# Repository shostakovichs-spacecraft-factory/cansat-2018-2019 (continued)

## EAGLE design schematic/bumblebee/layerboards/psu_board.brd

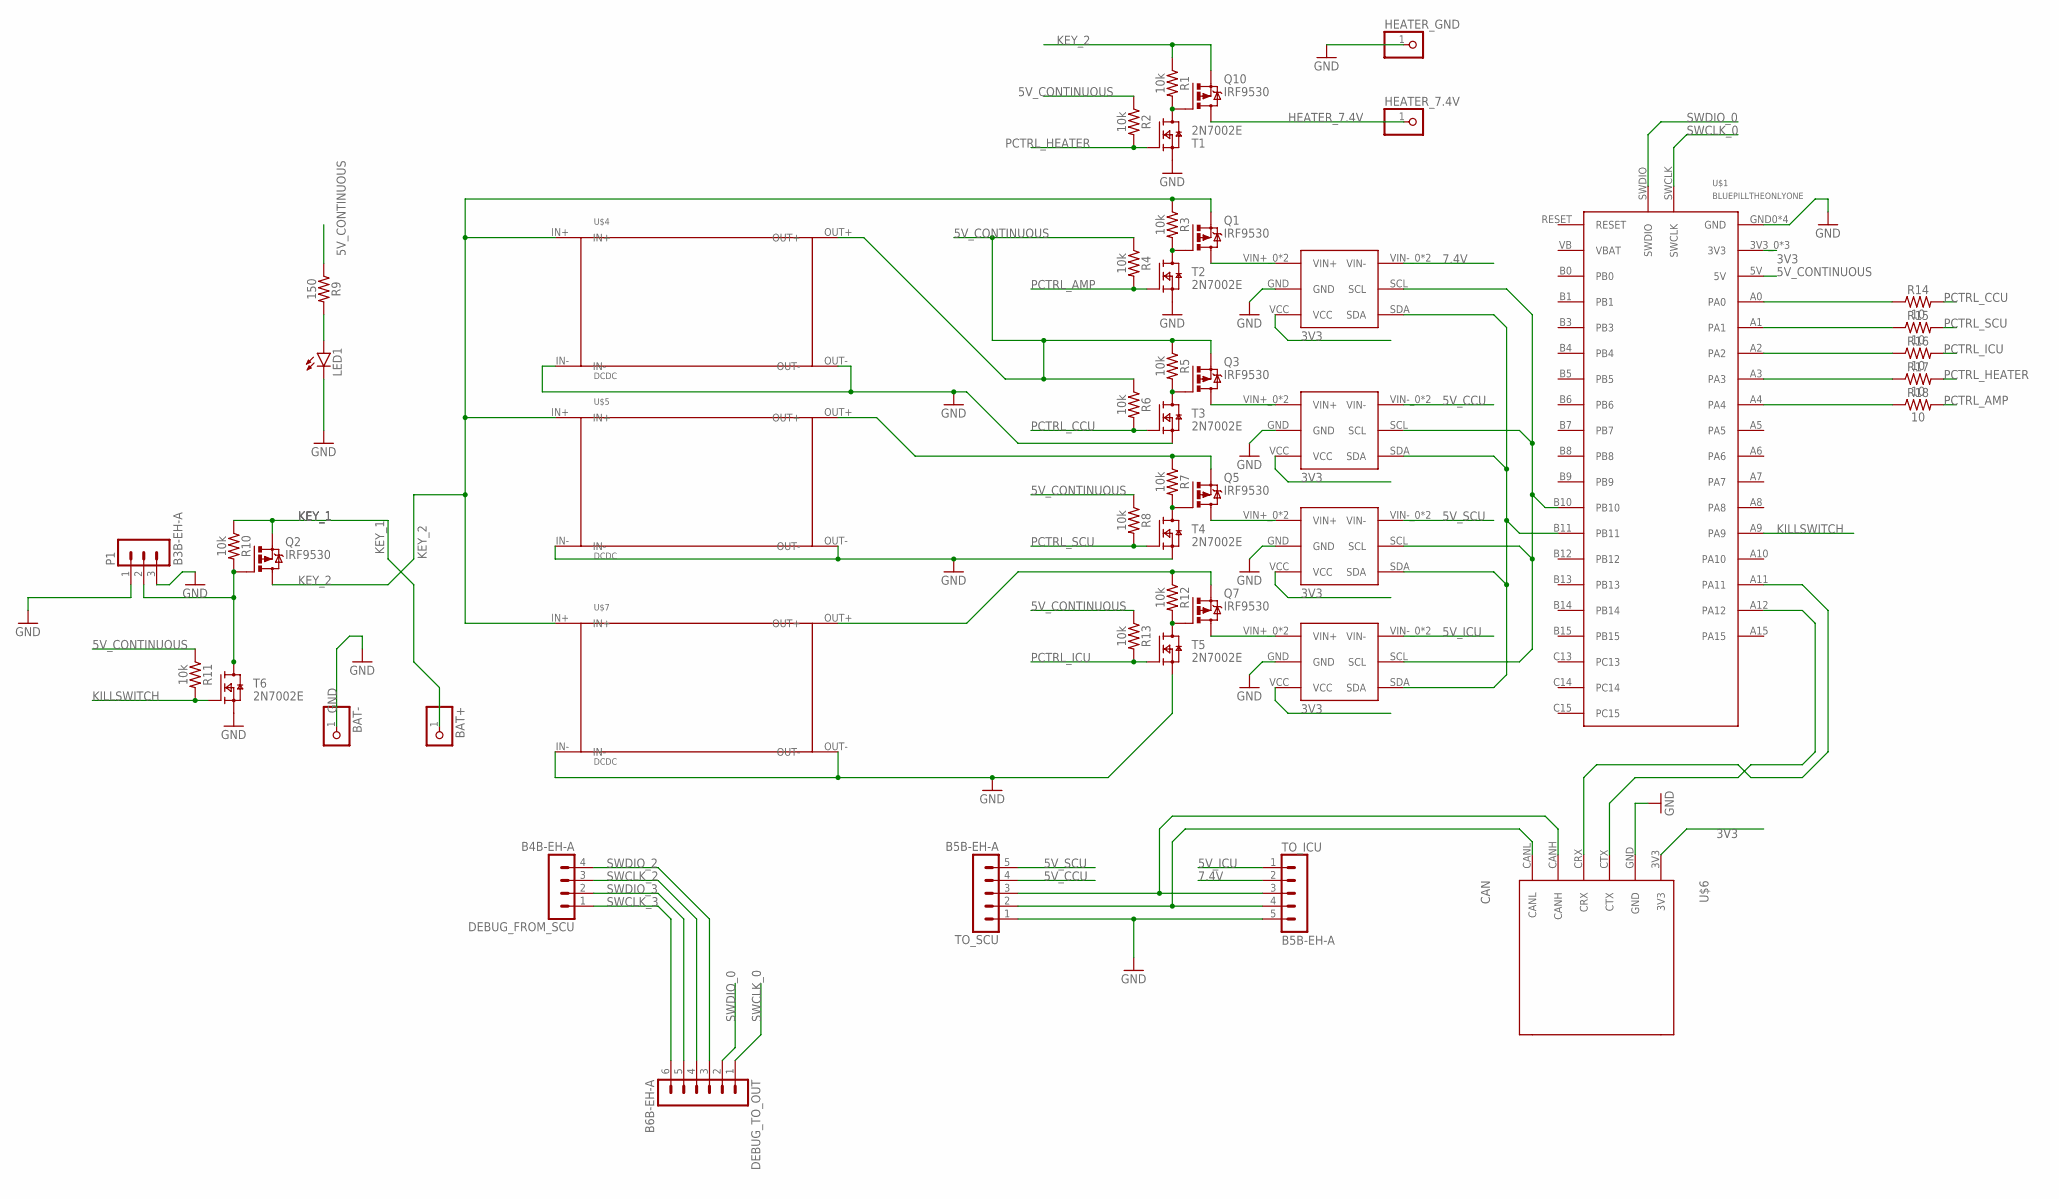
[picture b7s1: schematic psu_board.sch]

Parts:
BAT+: PINHD-1X1; 1X01
BAT-: PINHD-1X1; 1X01
DEBUG_FROM_SCU: B4B-EH-A
DEBUG_TO_OUT: B6B-EH-A
HEATER_7.4V: PINHD-1X1; 1X01
HEATER_GND: PINHD-1X1; 1X01
LED1: LED5MM
P1: B3B-EH-A
Q1, Q2, Q3, Q5, Q7, Q10: IRF9530; TO220BV
R1, R2, R3, R4, R5, R6, R7, R8, R10, R11, R12, R13: 10k; AXIAL-0.3
R9: 150; AXIAL-0.3
R14, R15, R16, R17, R18: 10; AXIAL-0.3
T1, T2, T3, T4, T5, T6: 2N7002E; SOT23
TO_ICU: B5B-EH-A
TO_SCU: B5B-EH-A
U$1: BLUEPILLTHEONLYONE; BLUEPIL
U$2, U$3, U$8, U$9: INA
U$4, U$5, U$7: DCDC
U$6: CAN

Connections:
3V3: U$1.3V3_0 (3V3), U$1.3V3_1 (3V3), U$1.3V3_2 (3V3), U$2.VCC, U$3.VCC, U$6.3V3, U$8.VCC, U$9.VCC
5V_CCU: TO_SCU.4, U$9.VIN-_0 (VIN-), U$9.VIN-_1 (VIN-)
5V_CONTINUOUS: Q3.S, R2.P$1 (1), R4.P$1 (1), R5.P$1 (1), R6.P$1 (1), R8.P$1 (1), R9.P$1 (1), R11.P$1 (1), R13.P$1 (1), U$1.5V, U$4.OUT+
5V_ICU: TO_ICU.1, U$2.VIN-_0 (VIN-), U$2.VIN-_1 (VIN-)
5V_SCU: TO_SCU.5, U$8.VIN-_0 (VIN-), U$8.VIN-_1 (VIN-)
7.4V: TO_ICU.2, U$3.VIN-_0 (VIN-), U$3.VIN-_1 (VIN-)
CANH: TO_ICU.3, TO_SCU.3, U$6.CANH
CANL: TO_ICU.4, TO_SCU.2, U$6.CANL
GND: BAT-.1, HEATER_GND.1, LED1.K (C), P1.1, P1.3, T1.2 (S), T2.2 (S), T3.2 (S), T4.2 (S), T5.2 (S), T6.2 (S), TO_ICU.5, TO_SCU.1, U$1.GND0 (GND), U$1.GND1 (GND), U$1.GND2 (GND), U$1.GND3 (GND), U$2.GND, U$3.GND, U$4.IN-, U$4.OUT-, U$5.IN-, U$5.OUT-, U$6.GND, U$7.IN-, U$7.OUT-, U$8.GND, U$9.GND
HEATER_7.4V: HEATER_7.4V.1, Q10.D
KEY_1: BAT+.1, Q2.S, R10.P$1 (1)
KEY_2: Q1.S, Q2.D, Q10.S, R1.P$1 (1), R3.P$1 (1), U$4.IN+, U$5.IN+, U$7.IN+
KILLSWITCH: R11.P$2 (2), T6.1 (G), U$1.A9
unnamed: Q1.G, R3.P$2 (2), T2.3 (D)
unnamed: U$1.A11, U$6.CRX
unnamed: Q5.G, R7.P$2 (2), T4.3 (D)
unnamed: Q7.G, R12.P$2 (2), T5.3 (D)
unnamed: Q5.S, R7.P$1 (1), U$5.OUT+
unnamed: Q3.G, R5.P$2 (2), T3.3 (D)
unnamed: Q7.S, R12.P$1 (1), U$7.OUT+
unnamed: Q1.D, U$3.VIN+_0 (VIN+), U$3.VIN+_1 (VIN+)
unnamed: Q3.D, U$9.VIN+_0 (VIN+), U$9.VIN+_1 (VIN+)
unnamed: Q5.D, U$8.VIN+_0 (VIN+), U$8.VIN+_1 (VIN+)
unnamed: Q7.D, U$2.VIN+_0 (VIN+), U$2.VIN+_1 (VIN+)
unnamed: U$1.B11, U$2.SDA, U$3.SDA, U$8.SDA, U$9.SDA
unnamed: U$1.B10, U$2.SCL, U$3.SCL, U$8.SCL, U$9.SCL
unnamed: U$1.A12, U$6.CTX
unnamed: LED1.A, R9.P$2 (2)
unnamed: Q10.G, R1.P$2 (2), T1.3 (D)
unnamed: R14.P$1 (1), U$1.A0
unnamed: R15.P$1 (1), U$1.A1
unnamed: R16.P$1 (1), U$1.A2
unnamed: R17.P$1 (1), U$1.A3
unnamed: R18.P$1 (1), U$1.A4
unnamed: P1.2, Q2.G, R10.P$2 (2), T6.3 (D)
PCTRL_AMP: R4.P$2 (2), R18.P$2 (2), T2.1 (G)
PCTRL_CCU: R6.P$2 (2), R14.P$2 (2), T3.1 (G)
PCTRL_HEATER: R2.P$2 (2), R17.P$2 (2), T1.1 (G)
PCTRL_ICU: R13.P$2 (2), R16.P$2 (2), T5.1 (G)
PCTRL_SCU: R8.P$2 (2), R15.P$2 (2), T4.1 (G)
SWCLK_0: DEBUG_TO_OUT.1, U$1.SWCLK
SWCLK_2: DEBUG_FROM_SCU.3, DEBUG_TO_OUT.4
SWCLK_3: DEBUG_FROM_SCU.1, DEBUG_TO_OUT.6
SWDIO_0: DEBUG_TO_OUT.2, U$1.SWDIO
SWDIO_2: DEBUG_FROM_SCU.4, DEBUG_TO_OUT.3
SWDIO_3: DEBUG_FROM_SCU.2, DEBUG_TO_OUT.5

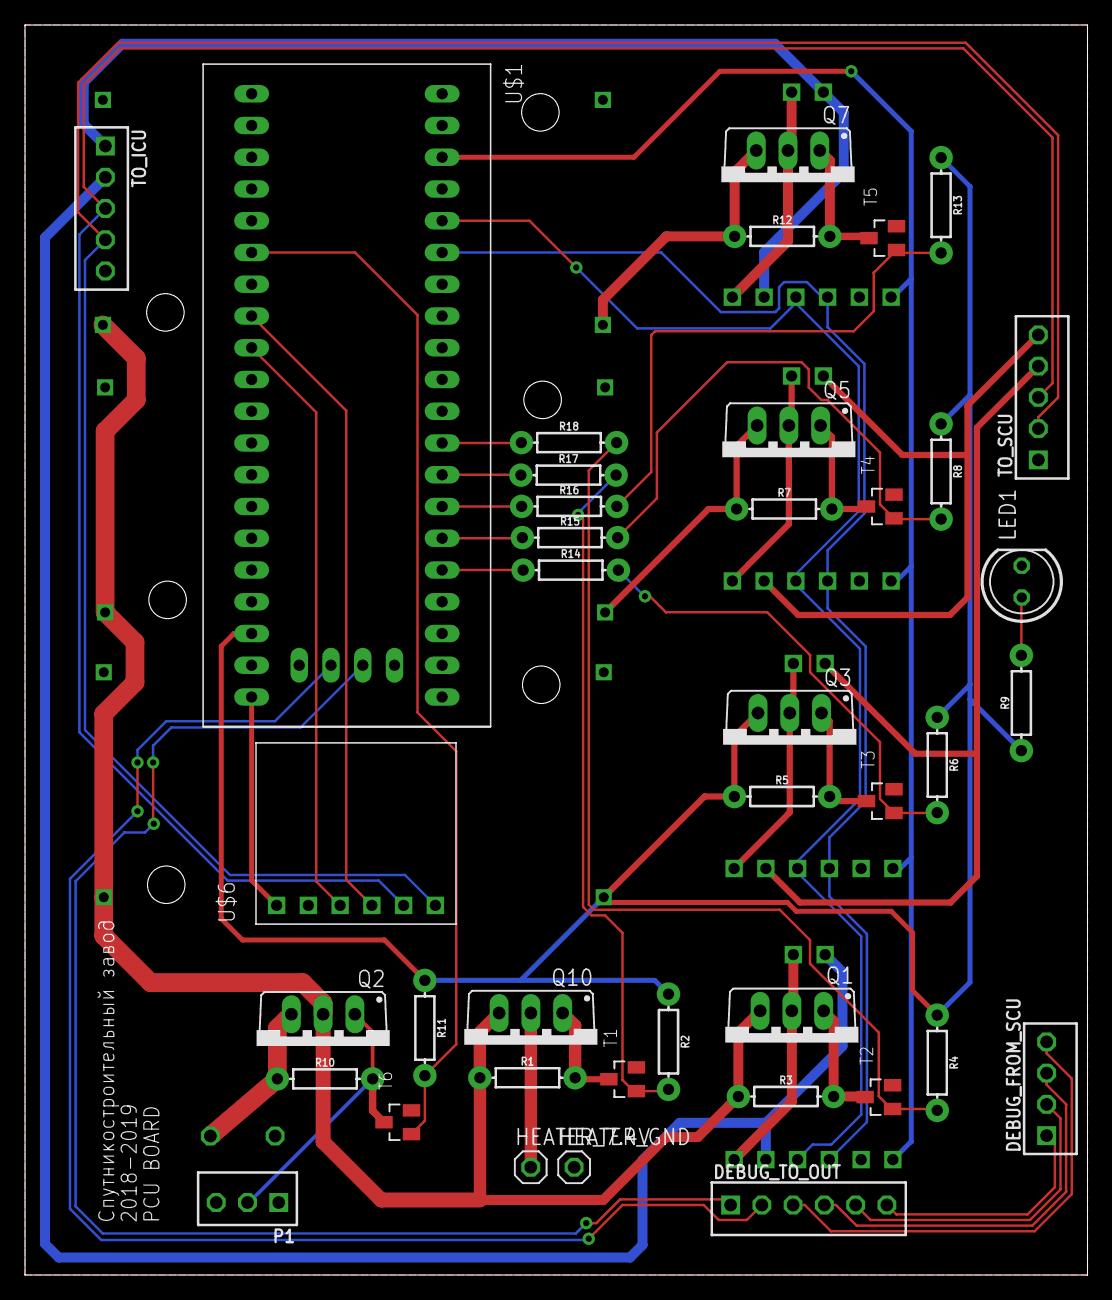
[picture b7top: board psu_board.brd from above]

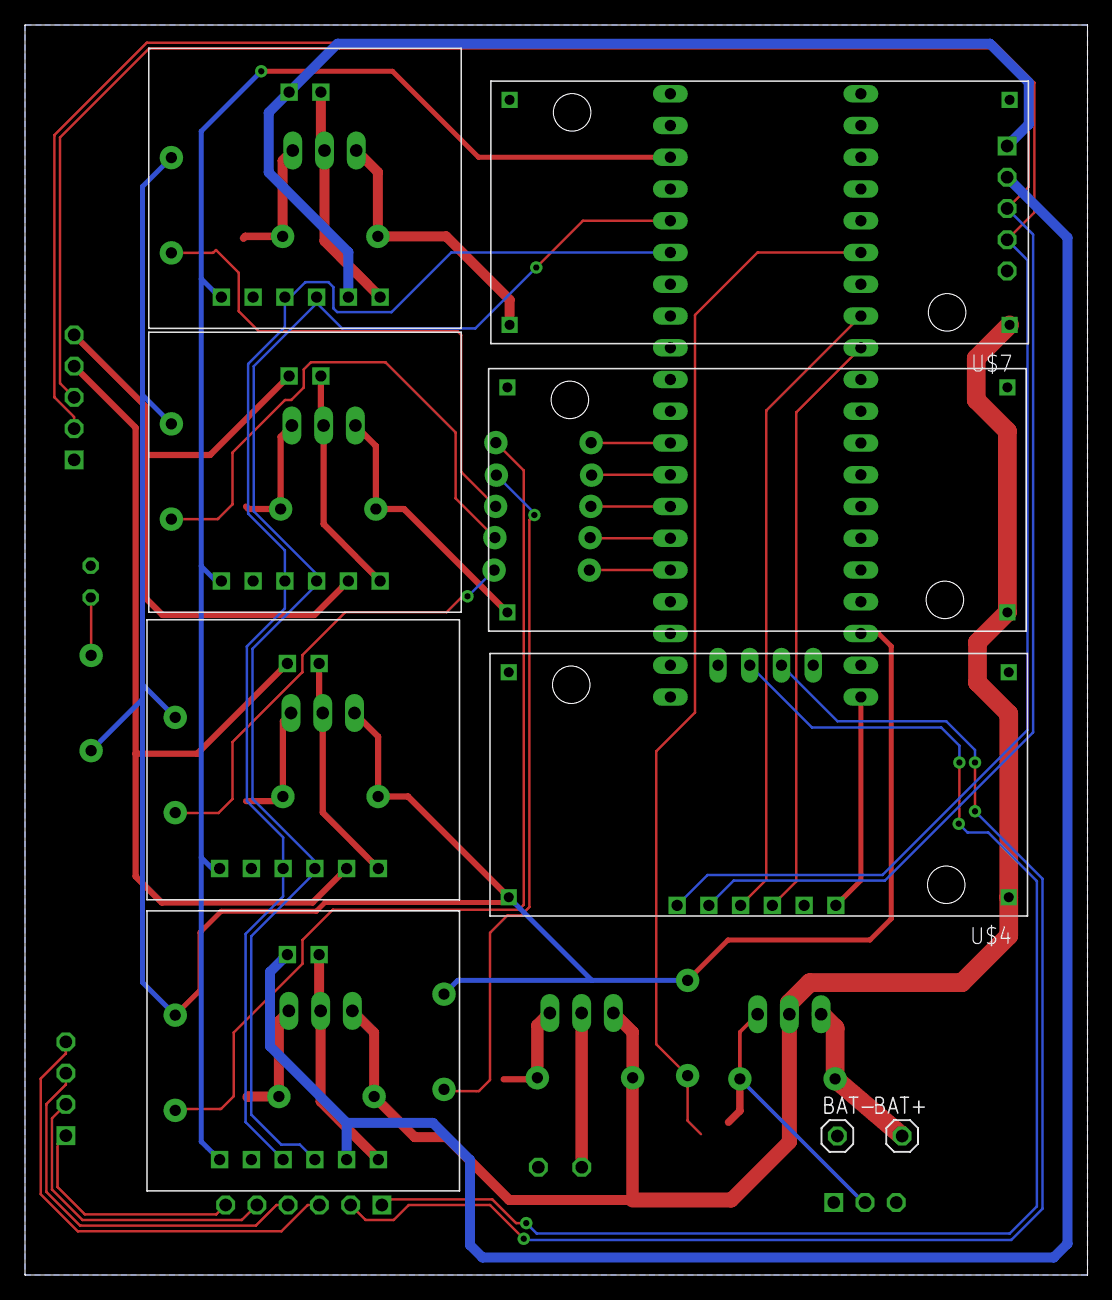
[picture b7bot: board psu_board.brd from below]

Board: 2 copper layers, 85.0 x 100.0 mm, 49 parts (9 on the bottom side), 46 nets.

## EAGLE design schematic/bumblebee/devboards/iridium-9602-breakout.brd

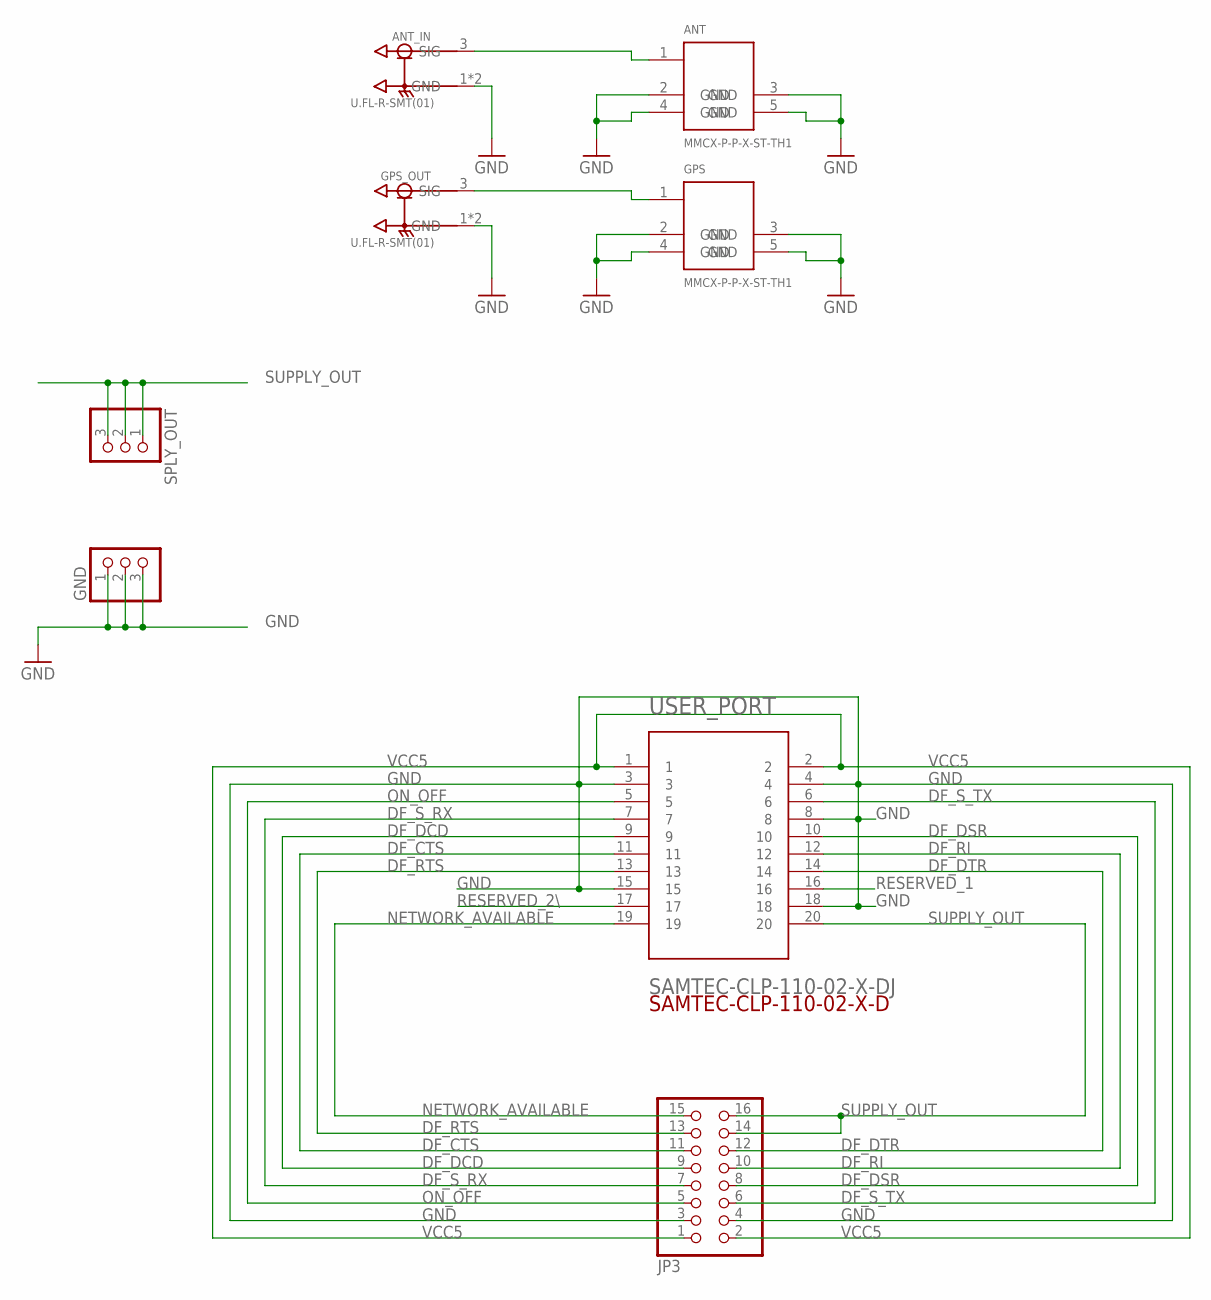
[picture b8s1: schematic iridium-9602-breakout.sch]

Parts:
ANT: MMCX-P-P-X-ST-TH1
ANT_IN: U.FL-R-SMT(01); HRS_U.FL-R-SMT(01)
GND: PINHD-1X3; 1X03
GPS: MMCX-P-P-X-ST-TH1
GPS_OUT: U.FL-R-SMT(01); HRS_U.FL-R-SMT(01)
JP3: PINHD-2X8; 2X08
SPLY_OUT: PINHD-1X3; 1X03
USER_PORT: SAMTEC-CLP-110-02-X-DJ; SAMTEC-CLP-110-02-X-D

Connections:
DF_CTS: JP3.11, USER_PORT.11
DF_DCD: JP3.9, USER_PORT.9
DF_DSR: JP3.8, USER_PORT.10
DF_DTR: JP3.12, USER_PORT.14
DF_RI: JP3.10, USER_PORT.12
DF_RTS: JP3.13, USER_PORT.13
DF_S_RX: JP3.7, USER_PORT.7
DF_S_TX: JP3.6, USER_PORT.6
GND: ANT.2 (GND), ANT.3 (GND), ANT.4 (GND), ANT.5 (GND), ANT_IN.1 (GND), ANT_IN.2 (GND), GND.1, GND.2, GND.3, GPS.2 (GND), GPS.3 (GND), GPS.4 (GND), GPS.5 (GND), GPS_OUT.1 (GND), GPS_OUT.2 (GND), JP3.3, JP3.4, USER_PORT.3, USER_PORT.4, USER_PORT.8, USER_PORT.15, USER_PORT.18
unnamed: ANT.1, ANT_IN.3 (SIG)
unnamed: GPS.1, GPS_OUT.3 (SIG)
NETWORK_AVAILABLE: JP3.15, USER_PORT.19
ON_OFF: JP3.5, USER_PORT.5
RESERVED_1: USER_PORT.16
RESERVED_2\: USER_PORT.17
SUPPLY_OUT: JP3.14, JP3.16, SPLY_OUT.1, SPLY_OUT.2, SPLY_OUT.3, USER_PORT.20
VCC5: JP3.1, JP3.2, USER_PORT.1, USER_PORT.2

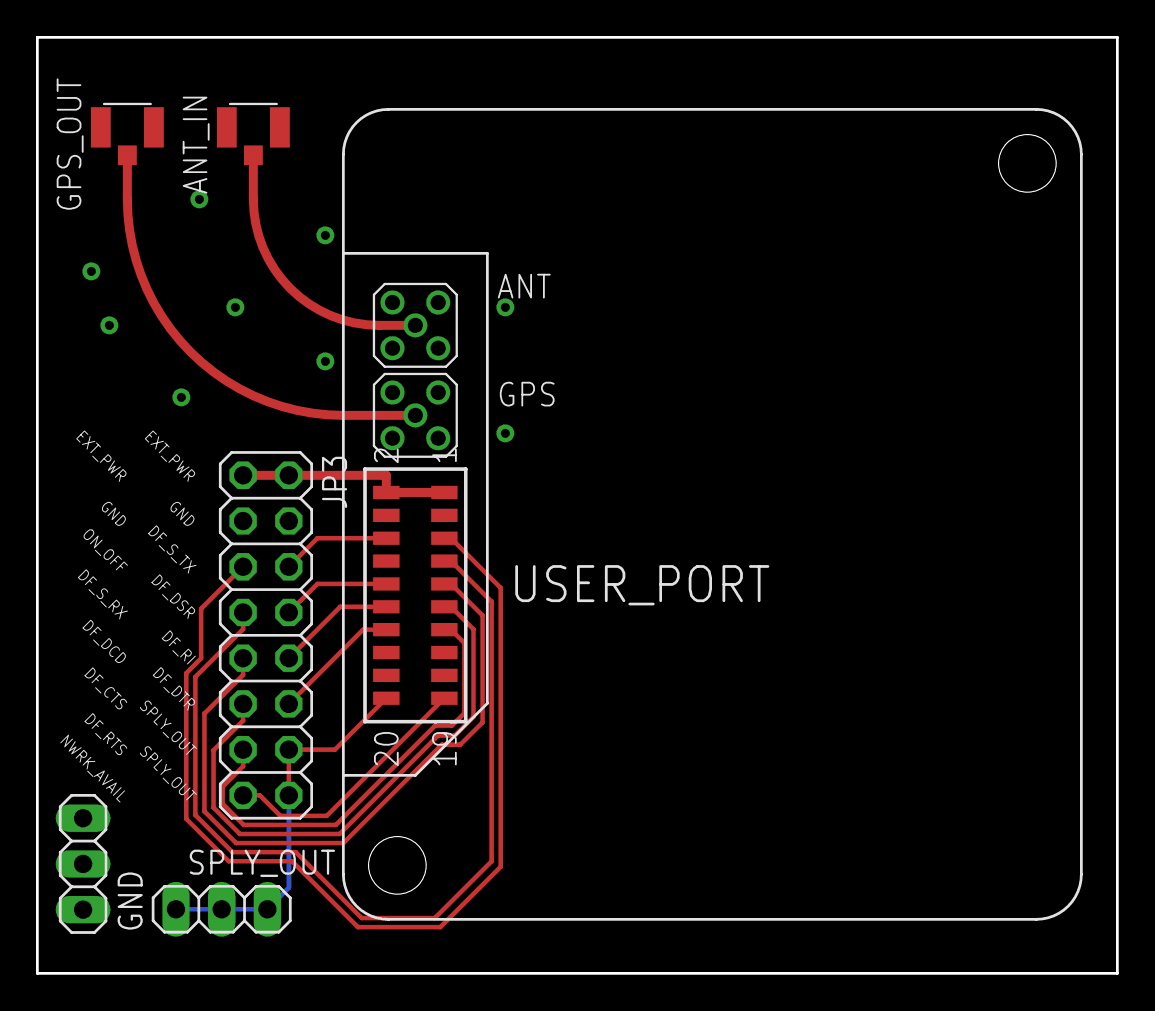
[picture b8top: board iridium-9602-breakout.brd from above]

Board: 2 copper layers, 60.0 x 52.0 mm, 8 parts (0 on the bottom side), 15 nets.

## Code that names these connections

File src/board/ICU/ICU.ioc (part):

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Mcu.Name=STM32F103V(C-D-E)Tx
Mcu.Package=LQFP100
Mcu.UserName=STM32F103VCTx
PA13.Mode=Serial_Wire
PA13.Signal=SYS_JTMS-SWDIO
PA14.Mode=Serial_Wire
PA14.Signal=SYS_JTCK-SWCLK
PB12.GPIOParameters=PinState,GPIO_Label
PB12.GPIO_Label=RADIO_NSS
PB12.PinState=GPIO_PIN_SET
PB12.Signal=GPIO_Output
PB13.Mode=Full_Duplex_Master
PB13.Signal=SPI2_SCK
PB14.Mode=Full_Duplex_Master
PB14.Signal=SPI2_MISO
PB15.Mode=Full_Duplex_Master
PB15.Signal=SPI2_MOSI
PB6.GPIOParameters=GPIO_Speed,PinState,GPIO_Label
PB6.GPIO_Label=LEDPIN
PB6.GPIO_Speed=GPIO_SPEED_FREQ_LOW
PB6.PinState=GPIO_PIN_RESET
PB6.Signal=GPIO_Output
PC10.Mode=SD_4_bits_Wide_bus
PC10.Signal=SDIO_D2
PC11.Mode=SD_4_bits_Wide_bus
PC11.Signal=SDIO_D3
PC12.Mode=SD_4_bits_Wide_bus
PC12.Signal=SDIO_CK
PC8.Mode=SD_4_bits_Wide_bus
PC8.Signal=SDIO_D0
PC9.Mode=SD_4_bits_Wide_bus
PC9.Signal=SDIO_D1
PD0.Mode=Master
PD0.Signal=CAN_RX
PD1.Mode=Master
PD1.Signal=CAN_TX
PD15.GPIOParameters=GPIO_Label
PD15.GPIO_Label=RADIO_IRQ
PD15.Signal=GPXTI15
PD2.Mode=SD_4_bits_Wide_bus
PD2.Signal=SDIO_CMD
PE12.GPIOParameters=GPIO_Label
PE12.GPIO_Label=RADIO_BUSY
PE12.Signal=GPIO_Input
PE13.GPIOParameters=GPIO_Speed,GPIO_Label
PE13.GPIO_Label=RADIO_TXEN
PE13.GPIO_Speed=GPIO_SPEED_FREQ_LOW
PE13.Signal=GPIO_Output
PE14.GPIOParameters=PinState,GPIO_Label,GPIO_ModeDefaultOutputPP
PE14.GPIO_Label=RADIO_NRST
PE14.GPIO_ModeDefaultOutputPP=GPIO_MODE_OUTPUT_OD
PE14.PinState=GPIO_PIN_SET
PE14.Signal=GPIO_Output
PE15.GPIOParameters=GPIO_Label
PE15.GPIO_Label=RADIO_RXEN
PE15.Signal=GPIO_Output
RCC.SYSCLKFreq_VALUE=72000000
RCC.SYSCLKSource=RCC_SYSCLKSOURCE_PLLCLK
board=custom

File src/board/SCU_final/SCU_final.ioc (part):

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Mcu.Name=STM32F103C(8-B)Tx
Mcu.Package=LQFP48
Mcu.UserName=STM32F103C8Tx
PA11.Mode=Master
PA11.Signal=CAN_RX
PA12.Mode=Master
PA12.Signal=CAN_TX
PA13.Mode=Serial_Wire
PA13.Signal=SYS_JTMS-SWDIO
PA14.Mode=Serial_Wire
PA14.Signal=SYS_JTCK-SWCLK
PA4.GPIOParameters=GPIO_Speed,PinState,GPIO_Label
PA4.GPIO_Label=BME_CS
PA4.GPIO_Speed=GPIO_SPEED_FREQ_HIGH
PA4.PinState=GPIO_PIN_SET
PA4.Signal=GPIO_Output
PA5.GPIOParameters=GPIO_Label
PA5.GPIO_Label=BME_SCK
PA5.Mode=Full_Duplex_Master
PA5.Signal=SPI1_SCK
PA6.GPIOParameters=GPIO_Label
PA6.GPIO_Label=BME_MISO
PA6.Mode=Full_Duplex_Master
PA6.Signal=SPI1_MISO
PA7.GPIOParameters=GPIO_Label
PA7.GPIO_Label=BME_MOSI
PA7.Mode=Full_Duplex_Master
PA7.Signal=SPI1_MOSI
PB10.GPIOParameters=GPIO_Label
PB10.GPIO_Label=MAG_SCL
PB10.Mode=I2C
PB10.Signal=I2C2_SCL
PB11.GPIOParameters=GPIO_Label
PB11.GPIO_Label=MAG_SDA
PB11.Mode=I2C
PB11.Signal=I2C2_SDA
PB12.GPIOParameters=GPIO_Speed,PinState,GPIO_Label
PB12.GPIO_Label=LSM_CS
PB12.GPIO_Speed=GPIO_SPEED_FREQ_HIGH
PB12.PinState=GPIO_PIN_SET
PB12.Signal=GPIO_Output
PB13.GPIOParameters=GPIO_Label
PB13.GPIO_Label=LSM_SCK
PB13.Mode=Full_Duplex_Master
PB13.Signal=SPI2_SCK
PB14.GPIOParameters=GPIO_Label
PB14.GPIO_Label=LSM_MISO
PB14.Mode=Full_Duplex_Master
PB14.Signal=SPI2_MISO
PB15.GPIOParameters=GPIO_Label
PB15.GPIO_Label=LSM_MOSI
PB15.Mode=Full_Duplex_Master
PB15.Signal=SPI2_MOSI
PB6.GPIOParameters=GPIO_Label
PB6.GPIO_Label=ADC_SCL
PB6.Mode=I2C
PB6.Signal=I2C1_SCL
PB7.GPIOParameters=GPIO_Label
PB7.GPIO_Label=ADC_SDA
PB7.Mode=I2C
PB7.Signal=I2C1_SDA
PC13-TAMPER-RTC.GPIOParameters=GPIO_Speed,PinState,GPIO_Label,GPIO_ModeDefaultOutputPP
PC13-TAMPER-RTC.GPIO_Label=LED
PC13-TAMPER-RTC.GPIO_ModeDefaultOutputPP=GPIO_MODE_OUTPUT_OD
PC13-TAMPER-RTC.GPIO_Speed=GPIO_SPEED_FREQ_HIGH
PC13-TAMPER-RTC.PinState=GPIO_PIN_SET
PC13-TAMPER-RTC.Signal=GPIO_Output
PD0-OSC_IN.Mode=HSE-External-Oscillator
PD0-OSC_IN.Signal=RCC_OSC_IN
PD1-OSC_OUT.Mode=HSE-External-Oscillator
PD1-OSC_OUT.Signal=RCC_OSC_OUT
RCC.SYSCLKFreq_VALUE=72000000
RCC.SYSCLKSource=RCC_SYSCLKSOURCE_PLLCLK
board=custom

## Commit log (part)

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2018-10-16 Папочка для моделей
2018-10-19 Add files via upload
    Часть деталек для тестов и замоделенная начинка
2018-10-21 Пара изменений
2018-11-15 Moving files
2018-11-16 Код поиска Солнца для модели
2018-11-17 Remake all light system && add graphic component
    Add new class for all light system functions
    It was important to make system much easier. So now you have to create
    new class instance, call just one function and be careful when it
    returns not a number
    Add graphic component
    Now you able to get all useful information from starting
2018-11-17 В тесте маджвика магнитометр на I2C
2018-11-17 Фоторезистор вынесен в отдельный модуль
2018-11-17 Изменение порядка сенсоров
2018-11-23 добавили тестовый проект для сериал порта на линуксе
2018-11-28 Создание интерфеса неспектральных камер
    Создан интерфейс для работы с uart под linux.
    Пока что нет способа изменить конфигурацию без перекомпиляции программы.
    Создан интерфейс для работы с камерами.
    Это прототип, так как не способен работать. Некоторые функции не
    подходят для работы на борту. Пока нет способа менять концигурацию во
    время выполения программы. Известные баги:
2018-11-29 Исправление ошибок
    - Наименование функции чтения изображения camera_get_and_save_picture
    изменена на camera_load_and_save_picture.
    - Теперь все функции делают то, что от них хотят.
    - Увеличен размер строки имени файла для уарта на 1.
2018-12-08 Добавление пары функции для удобной работы на миникомпьютере Рнаьше была лишь одна функция для сохранения изображения. Она загружала и сразу сохраняла его, занимая все процессорное время. Теперь есть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
2018-12-11 Добавлвены требования к надежности (их нет) Добавлены требования к живучести НИП-а Поправлена структура ТЗ
2018-12-22 Наработки Арины для схемы
2018-12-28 Реструткуризация иглового проекта
2018-12-28 Добавление описания взаимодействия протоколов
    В целом, описано, где какой протокол используется. Есть пара элементов, которые стоило бы доделать. Также не уверен в необходимости описания самих протоколов. Поэтому их тут нет.
2018-12-28 Обновление схемы протоколов
    Сделал схему красивее
2018-12-29 Полная переработка описания протоколов
    Все переделано с учетом всех замечаний
2019-01-03 Мелкие изменения
    Новая цветовая гамма. Добавлена главная страница. Маленькие корректировки.
2019-01-06 Squashed commit of the following:
    commit bbe75f2ba636e86ea759fc0c795d406c2297ca99
    Author: Kirs67 <kirilel200267@gmail.com>
    Date: Mon Jan 7 01:16:28 2019 +0300
    Исправлена INA
    commit 84fcf59dae87e7c5b0b953ea137079167e3747d4
    Author: Kirs67 <kirilel200267@gmail.com>
2019-01-09 Модель аппарата на момент 09.01.19
    apparat.asm -- сборка аппарата, остальное -- его элементы
2019-01-10 Добавил протокол совещания (!) от 10.01.18
2019-01-11 Добавлена схема платы SCU
2019-01-11 Комментарии в презентации по обсуждениям
2019-01-14 Платка для отладки радиомодуля
2019-01-14 Визуальное улучшение
    Я познал красоту. Теперь вы можете увидеть, насколько стало яснее, приятнее и точнее.
2019-01-15 Платка для антенны иридиума
2019-01-16 Мелкие правки перед отправкой на изготовление
2019-01-16 "Структурная" схема и правки названий в схеме соединений
2019-01-16 Правка орфографии
2019-01-17 Красивые переименования
2019-01-18 Косяки с вложенностью разделов
2019-01-18 Схемы за последнее время
2019-01-18 Орфография везде
2019-01-28 Малые корректировки
    - Удалено "LoRaWan"
    - Малые корректировки
2019-01-28 Малые корректировки
2019-01-28 Исправлены замечания Вячеслава по ТЗ, кроме пункта 5 замечаний по СЧ ОКР Зонд Некоторые другие исправления ТЗ Исправленная схема электроники
2019-01-29 Предфинальная правка
    Добавлена нумерация.
    Новые главы начинаются с нового листа
    Добавлена штука как в титульных дистах других документов
2019-01-30 Актуальная версия сборки в виде архива
2019-01-30 Финальная версия
2019-01-30 удалено лишнее
2019-01-30 приложения к ПЗ теперь в порядке
2019-02-03 И пдф финальных версий тоже
2019-03-14 Little play with .gitignore
2019-03-15 Little play with gitignore 3
2019-03-24 Added mavlink distribution (with Granum's definition as example)
2019-03-24 Added first draft of canmavlink (not tested yet) and test project for CAN on bluepill
2019-03-24 Рефакторинг функций матриц и добавление деинициализации LDR
    Функции транспозиции и инверсс теперь принимают лишь один параметр и
    соотвественно результат остается в этом же параметре. Код стал выглядеть
    приятно.
    Появилась деинициализация LDR. Нам будет не хватать сотен мегабайт
    неосвобожденной памяти.
2019-03-25 Added zikush' mavlink definitions
2019-03-27 Canmavlink is working (only one test conducted)
2019-03-30 Исправлние ошибок, добавление функций
    Исправлены ошибки, из-за которых предыдущая версия не компилилась.
    Добавлены функции сложения матрицы, и нахождения нормы.
    Причесан файл matrix.h. Он стал более читаемым.
2019-03-30 Создание модуля AHRS
    Без комментариев
2019-04-05 добавлены технологические правила резонита
2019-04-06 Изменение всего в Маджвике, добавление кватернионов и +функция в матрицах
    Скопировал кватернионы у Кирилла, добавил пару функций, и изменил
    навзания старых. Также исправил функцию инверсии.
    Связал вместе матрицы, векторы и кватернионы функциями конверсии.
    Добавил функцию в матрицы для проверки размеров функции.
    Заменил везде AHRS на madgwick для добваления нового модуля в будущем.
    Т
2019-04-06 Переещение исходников в src/
2019-04-06 Sitched to HAL and CubeMX on ICU, started writing sx1262 driver
2019-04-06 Рабочая версия (возможно)
    Испарвлено все, что могло быть исправлено. Теперь ahrs работает,
    как и обычный маджвик по крайней мере для связки accel+mag. Гироскоп
    и свет будет теститься в далнейшем.
2019-04-10 Готовая плата ICU. Стоит посмотреть ещё раз и проверить
2019-04-12 Добавил шаблон для CAM задачи для подготовки исходных данных для Резонита
2019-04-12 Прихорошил плату ICU
2019-04-13 Добавлена возможность создавать несколько ahrs процессов
    Структура параметров трансформировалась в структуру-дескриптора
    ahrs процесса. Так что теперь можно сделать несколько ahrs
    процессов. Один будет обычным маджвиком, второй без магнитометра,
    но со светом, а третий может быть со всем вместе.
2019-04-13 Исправление заливки в символах нашей библиотеки
    А еще удаление оттуда иридиума и исправление SCU
2019-04-13 Продолжается работа над платами. Обновлены компоненты в библиотеках - удалены полигоны в TPLACE. Обновлены компоненты на некоторых платах
2019-04-17 Transceiver is ready for test
2019-04-19 CCU и ICU полностью готовы. Было бы здорово, если бы ещё кто-то посмотрел По SCU требуются уточнения
2019-04-21 Готова SCU и поправил lsm303c в либе
2019-04-23 "порядок" в библиотеках
2019-04-24 Подготовка плат к производству
2019-04-25 Working with transceiver (still not working)
2019-04-26 Начата работа над PCU и в частности над инами
2019-04-27 Добавлена BME280
    Код рабочий на 95%. 5% - одна из бмешек не хочет нормально давать
    нам влажность.
2019-04-27 На этом драйвер для ины готов
2019-05-02 Transceiver is working (Actually, this code is tested only for transmitting, receiveing part was done by RPi and spidev-based script)
2019-05-02 Сделана платка PCU, осталось развести. Добавлена ещё одна либа для игла
2019-05-03 Finally finished with PCU. Pls check it
2019-05-04 Гораздо более рабочая версия. Вроде даже способна получать сообщения от гейтвея, но интерфейсы еще не проработаны
2019-05-04 Мелкие украшательства
2019-05-04 Ported sx1268 driver tor RPi
2019-05-04 big endian!
2019-05-05 Украшательства и исправления
2019-05-05 Наброски бортового модуля для взаимодействия с модемом
2019-05-07 Что-то начинает прояснятся в структуре драйвера
2019-05-07 Забытый комментарий
2019-05-08 Правки по PSU
2019-05-08 Доулучшен код для ads
    Теперь все работает!!!!
2019-05-08 Добавлены некоторые события и они даже парсятся
2019-05-09 Парсилка событий теперь на что-то похожа
2019-05-09 Убаны "лишние" команды
2019-05-10 Все платы готовы и отправлены в резонит
2019-05-10 Добавлены модули 1wire, ds18b20, Time
    1wire и ds18b20 скопированы и подстроенны под нашу систему по
    лицензионному соглашению.
    Модуль Time вмещает в себя функцию для delay в микрсекундах.
2019-05-11 ICU as CAN-TO-RADIO bridge is almost done
2019-05-12 ICU can now serve as CAN-RADIO bridge Also did some preparations for gcs
2019-05-12 Исправил баг с Hard fault
2019-05-14 Исправил библиотеку Осталось исправить внешнюю плату и сделать плату под антенну GPS
2019-05-18 CAN on SCU is working now
2019-05-19 Latest changes to ICU and SCU (made for May video)
2019-05-25 Working on ground station
2019-05-31 Latest experiments with grain mcc
2019-05-31 CCU's spectrum handling is half-done
2019-06-01 Переделал драйвер Василия
2019-06-02 System is prepared for full-way spectrum tests!
2019-06-06 Драйвер для lsm6ds3 теперь работает
    - Пофиксин баг в коде Василия.
    - Выбраны удобные стандартный настройки.
    - Правильно настроен SPI.
2019-06-07 Магнитометр работает!
2019-06-08 ICU routing done (only sd tested)
2019-06-10 PCU code seems to be done and ready for tests
2019-06-12 Добавлена жесткая калибровка магнитометра
2019-06-13 Dealed with small bug in radio reception code, minor changes to ground station (adopted to changes in redis-py and (I hope) fixed an issue with charts jumping in time)
2019-06-14 Что-то по платам
2019-06-15 GCS plate ready
2019-06-19 CCU code right before simplification (stiill doesn't work)
2019-06-20 CCU camera part ready
2019-06-21 Скопирован код под камеры из research
    Этот код частично адаптирован. С камерой есть связь, но слегка ломаная.
2019-06-23 Improved radio and debugged PCU
2019-06-24 Камера заработала
2019-06-24 Почти ок код под камеры
2019-06-25 Some work done on 25.06
2019-06-25 Some efforts on migrating to FreeRTOS (not done yet)
2019-06-25 Иридиум начал переезжать на ICU
2019-06-25 Completely ported existing ICU functionality to work on FreeRTOS
2019-06-26 Теперь точно интегрирована
2019-06-27 Cleaned all the mess in CCU and added board-wide CAN tickrate setting (not implemented on SCU, cause it's still VERY messy)
2019-06-27 Почти готово?
2019-06-28 Added gps parsin and some required MAVlink messages
2019-06-28 Баги пойманы
2019-06-28 Опечатка
2019-06-29 Refactored SCU Only environmental sensors in a main(), we still need to deal with inertial navigation system
2019-06-29 Master is up to date
2019-06-29 Рабочий маджвик на минималках
2019-06-29 Команда на управление делителем отправки иридиума и её обработка в ICU; изменение ICU_STATS
2019-06-29 Более безопансные значения конфига для иридиума (на всякий случай)
2019-06-29 Добавлена глобальная структура для подсчета пакетов в ICU
2019-06-29 Один минибаг в роутере убит и предотвращена рассылка входящих сообщений на шину
2019-06-29 Иридиевый таск и хартбит возвращен к запуску Все хэндлы инициализированны в NULL Увеличен стэк heartbeat таска (теперь ему не хватит минимума) Добавлен более осторожный роутинг на случай, если какие-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
2019-06-29 Иридиевый таск не затрет входящее сообщение в очереди, если к нам придет "вхоядщее" сообщение с неба
2019-06-30 Иридиевый таск флушит RX буфер перед начало SBD сессии, чтобы смыть оттуда потенциально накопленный мусор
2019-07-01 Наловлены баги в иридиуме
2019-07-01 Debugging stuff - revert later
2019-07-02 Small fix
2019-07-02 Код под камеры встроен и типа должен работать
    Отвечаю
2019-07-02 Fixed and improved CAN communication
2019-07-02 Backported needed changes
2019-07-02 Убрал мусор
2019-07-02 /bin/bash круче чем /bin/sh
2019-07-02 На грейне питон то 3.5, а не 3.7
2019-07-02 Формат лога правильный
2019-07-03 Something has been done, idk what, but need to commit before implementing usart CCU_ICU backbone
2019-07-03 BME280 написан под SPI
2019-07-03 Новый проект под новое SCU
2019-07-03 ADS1115 тоже похож на рабочий
2019-07-03 lsm6ds3 присоединяется к коллективу "работающих"
2019-07-03 забытые файлы
2019-07-03 Временный коммит
2019-07-03 bme280 теперь точно работает
2019-07-03 Все готово для проверки в полной системе - Интегрировал mavlink+can - Добавил магнетометр и ahrs
2019-07-04 Added camera backbone
2019-07-04 Bug fix 1
